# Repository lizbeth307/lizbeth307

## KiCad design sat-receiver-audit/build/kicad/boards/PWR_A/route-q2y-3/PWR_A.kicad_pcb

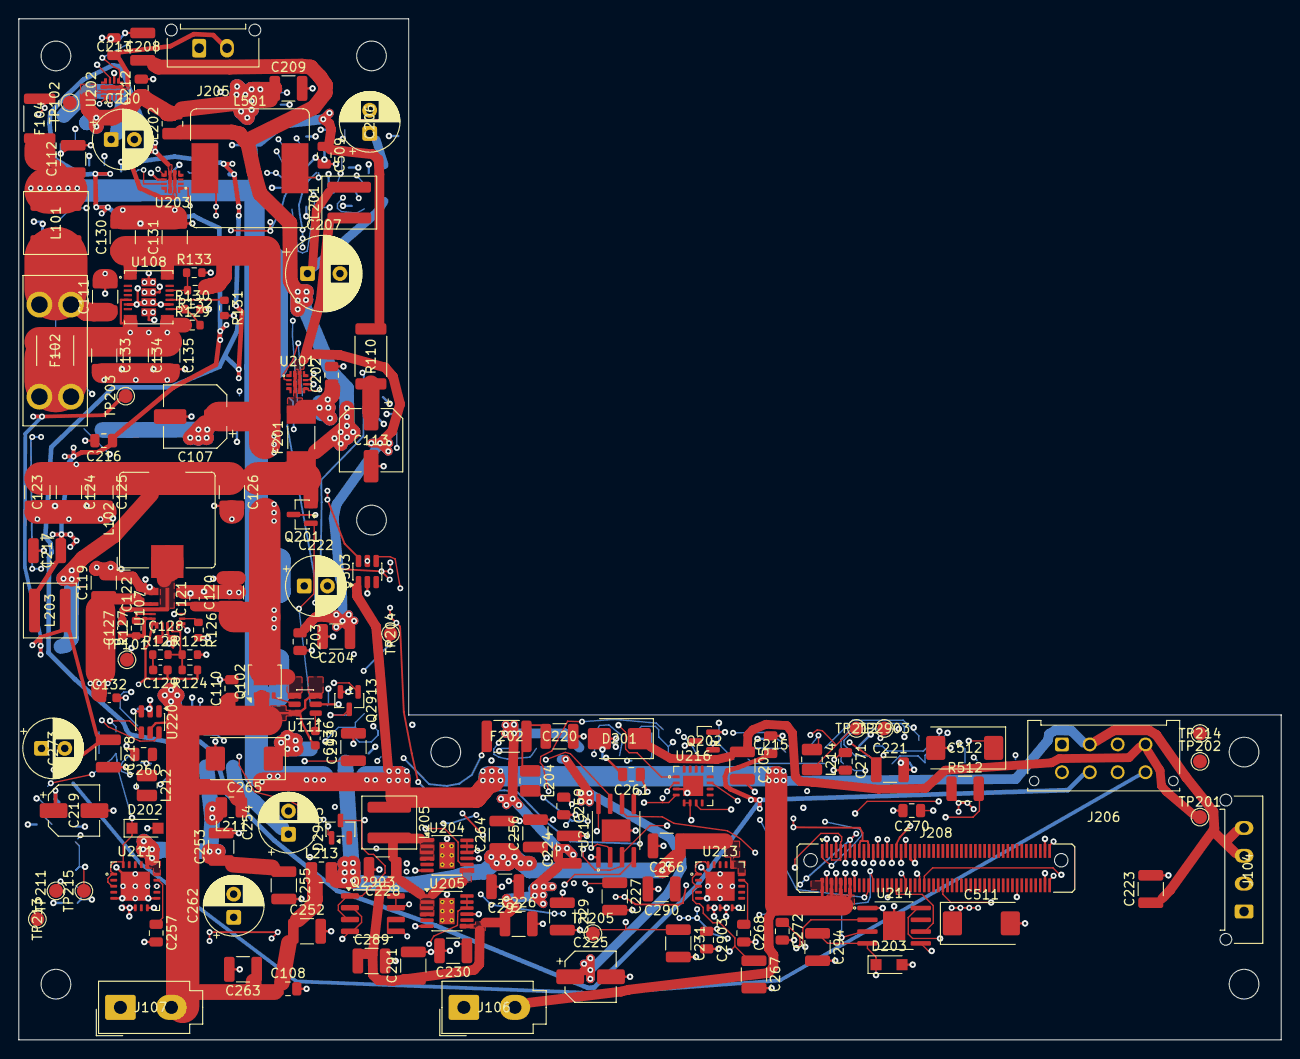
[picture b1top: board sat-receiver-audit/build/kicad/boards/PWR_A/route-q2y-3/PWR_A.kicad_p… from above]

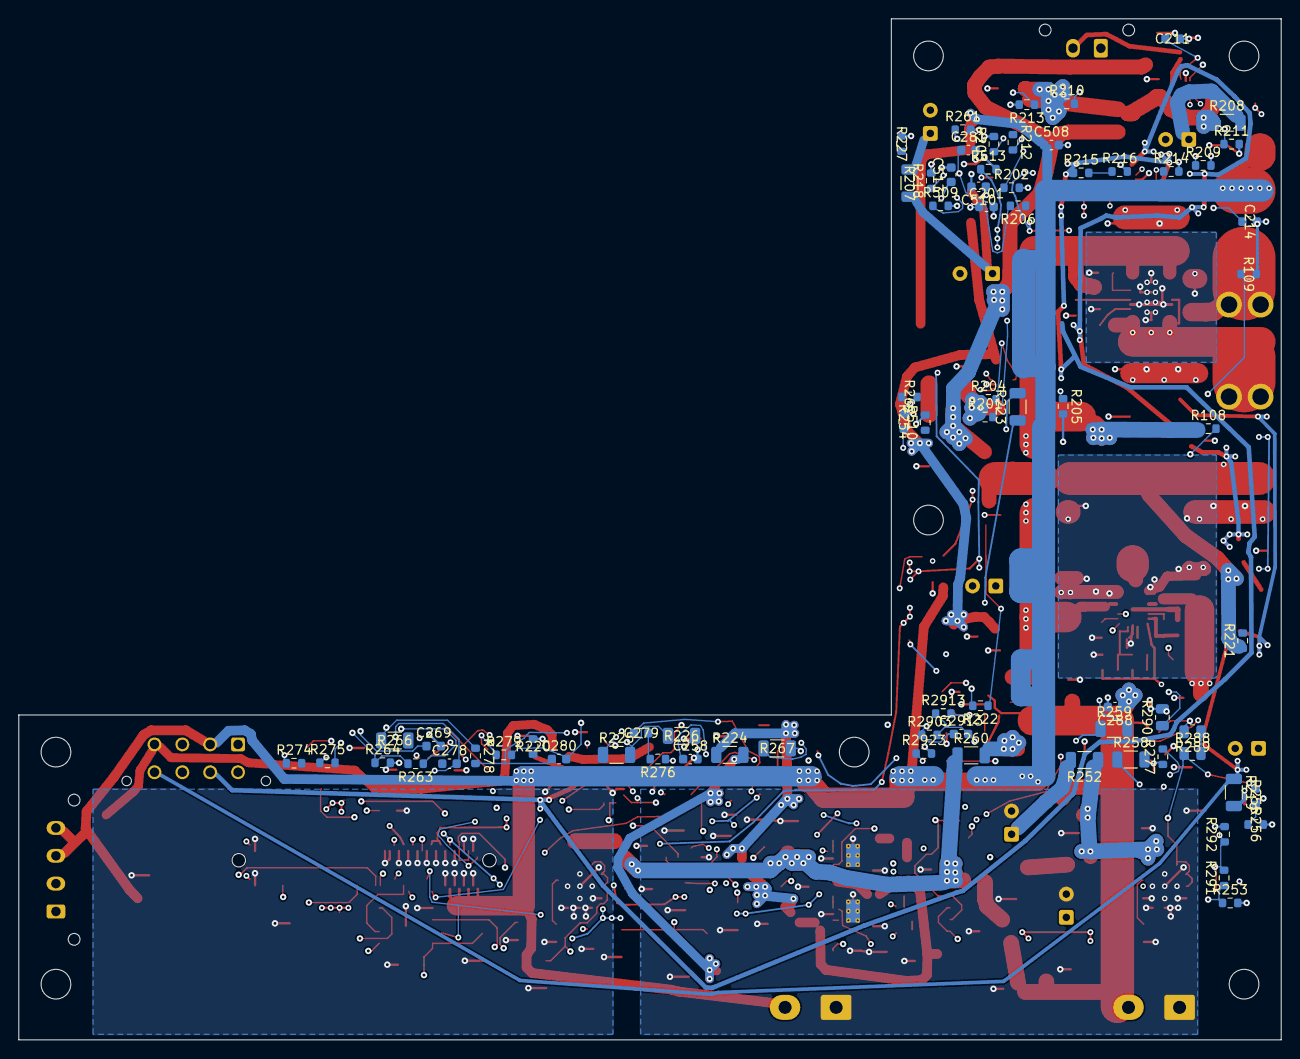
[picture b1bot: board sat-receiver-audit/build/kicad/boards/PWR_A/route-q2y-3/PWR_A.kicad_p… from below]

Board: 6 copper layers, 136.0 x 110.0 mm, 233 parts (73 on the bottom side), 113 nets.

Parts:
C107: 100µF35VlowESR; CP_Elec_6.3x7.7
C108, C110: 1µF50VX7R; C_0805_2012Metric
C111, C112, C123, C124, C125, C126: 22µF50VX7R 1210 C3225X7R1H226M250AC; C_1210_3225Metric
C113: 16SVPC100M 100 µF 16 V ±20% OS-CON; CP_Elec_6.3x5.9
C119, C120, C130, C131: 10µF50VX7R 1210; C_1210_3225Metric
C121, C122, C132: 100nF50VX7R; C_0603_1608Metric
C127: 100nF50VX7R CBOOT; C_0603_1608Metric
C128: 1µF16VX7R CVCC; C_0603_1608Metric
C129: 4.7pF50VC0G CFF; C_0603_1608Metric
C133, C134, C135: 47µF10VX7R 1210; C_1210_3225Metric
C136: 100nF50VX7R VCAP; C_0603_1608Metric
C201, C211, C214: 3.3nF 50V C0G C1608C0G1H332J080AA; C_0603_1608Metric
C202, C203, C212, C213, C215, C216, C257, C259, C260, C261, C268, C270, C271, C272, C2903: 1uF 50V X7R C2012X7R1H105K125AB; C_0805_2012Metric
C204, C205, C208, C209, C217, C218, C220, C221, C226, C228, C230, C252, C253, C255, C263, C264, C266, C289, C291: 10uF 50V X7R C3225X7R1H106K250AC; C_1210_3225Metric
C206, C210, C222, C254, C262, C273: 47uF 50V EEUFR1H470; CP_Radial_D6.3mm_P2.50mm
C207: 220uF/25V UHE1E221MPD; CP_Radial_D8.0mm_P3.50mm
C219, C225: 47uF 10V 16SVPG47M; CP_Elec_5x4.5
C223, C224, C227, C229, C231, C256, C267, C290, C292, C293, C294: 22uF 50V X7R C3225X7R1H226M250AC; C_1210_3225Metric
C258: 47nF 50V X7R C1608X7R1H473K080AA; C_0603_1608Metric
C265: 47uF 35V 35TQS47MEX; CP_EIA-7343-15_Kemet-W
C269, C278, C279, C280, C281, C288, C2913: 100nF 50V X7R C1608X7R1H104K080AA; C_0603_1608Metric
C508, C513: 100nF X7R 10V; C_0603_1608Metric
C509: 4.7uF X7R 10V; C_0805_2012Metric
C510: 1uF X7R 10V; C_0603_1608Metric
C511: 100uF 16V 16TQC100MD2; CP_EIA-7343-20_Kemet-V
C512: 220uF 16V 16TQC220MD3; CP_EIA-7343-31_Kemet-D
D201: SMBJ13A-E3/52; D_SMB_KA
D202, D203: PMEG4030ER; Nexperia_CFP3_SOD-123W
D2903: BZX84C10-7-F; SOT-23
F102: 4 A DC ≥32 V LAB5; Fuseholder_Blade_Mini_Keystone_3568
F104, F202: MF-MSMF075/24-2 0.75A; Fuse_1812_4532Metric
F201: Littelfuse 0451004.MRL 4A; Fuse_Littelfuse-NANO2-451_453
H1, H2, H3, H4, H5, H6, H7: NPTH_3.2mm
J104: X02P1-PWR: Molex Micro-Fit 3.0 4, верхній вхід, S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; Molex_Micro-Fit_3.0_43650-0415_1x04_P3.00mm_Vertical
J106: X42J2-PWR: Molex Mini-Fit Jr. 2×1, верхній вхід, 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; Molex_Mini-Fit_Jr_5566-02A_2x01_P4.20mm_Vertical
J107: X42J1-PWR: Molex Mini-Fit Jr. 2×1, верхній вхід, 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; Molex_Mini-Fit_Jr_5566-02A_2x01_P4.20mm_Vertical
J205: X19P1-PWR: Molex Micro-Fit 3.0 2, верхній вхід, S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; Molex_Micro-Fit_3.0_43650-0215_1x02_P3.00mm_Vertical
J206: SL2-PWR-MF: Molex Micro-Fit 3.0 2×4, верхній вхід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; Molex_Micro-Fit_3.0_43045-0812_2x04_P3.00mm_Vertical
J208: B2B-PWRA: Samtec LSHM-150 2×50, PWR-A верх, стик 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; Samtec_LSHM-150-xx.x-x-DV-N_2x50_P0.50mm_Vertical
L101: XAL6060-103MEC 10 µH ±20%; L_Coilcraft_XAL6060-XXX
L102: SRP1040VA-4R7M 4.7 µH ±20%; L_Bourns_SRP1038C_10.0x10.0mm
L201, L203, L205: 1uH XAL5030-102MEC; L_Coilcraft_XAL5030-XXX
L202, L204, L211, L212, L213, L214: 1uH SRP2510PA-1R0M; L_1008_2520Metric
L501: SRR1260-101M 100uH; L_Bourns_SRR1260
Q102: DMT6007LFG-7; Diodes_PowerDI3333-8
Q201: AO3407A; SOT-23
Q202, Q2913: 2N7002; SOT-23
Q2903: DMP6050SSD-13; SOIC-8_3.9x4.9mm_P1.27mm
R108, R132: 1.00M1%; R_0603_1608Metric
R109: 115k1%; R_0603_1608Metric
R110: WSL2512R3300FEA 0.330 Ω 1%; R_2512_6332Metric
R124: 100k1%; R_0603_1608Metric
R125: 9.09k0.1%; R_0603_1608Metric
R126, R131: 14.3k1%; R_0603_1608Metric
R127: 100Ω1% RBOOT; R_0603_1608Metric
R128: 1.00k1% RFF; R_0603_1608Metric
R129: 40.2k1%; R_0603_1608Metric
R130: 10.0k1%; R_0603_1608Metric
R133: 147k1%; R_0603_1608Metric
R201, R213, R218, R220, R253, R261, R292, R2903: 100k 1%; R_0603_1608Metric
R202: 13.0k 1% 100ppm; R_0603_1608Metric
R203: 825R 1%; R_0603_1608Metric
R204, R210: 102k 0.1%; R_0603_1608Metric
R205, R211, R216: 10.0k 0.1%; R_0603_1608Metric
R206, R212, R221, R222, R2923: 10.0k 1%; R_0603_1608Metric
R207, R208, R223, R252, R259, R260, R267: 0.22R 1% 0.25W; R_1206_3216Metric
R209: 1.96k 1%; R_0603_1608Metric
R214: 1.65k 1%; R_0603_1608Metric
R215: 19.6k 0.1%; R_0603_1608Metric
R219, R224: 0.15R 1% 0.25W; R_1206_3216Metric
R225, R226: 20mR 1% 0.25W; R_1206_3216Metric
R227: 21.5k 0.1% 25ppm; R_0603_1608Metric
R254: 2.05k 1%; R_0603_1608Metric
R255: 110k 0.5%; R_0603_1608Metric
R256: 10.0k 0.5%; R_0603_1608Metric
R258: 0.100R 0.1% 0.25W Kelvin; R_1206_3216Metric
R262: 7.15k 1% 100ppm; R_0603_1608Metric
R263: OVLO TBD (start 102k 0.1%); R_0603_1608Metric
R264: OVLO TBD (start 9.09k 0.1%); R_0603_1608Metric
R266: 0.200R 0.1% 0.25W Kelvin; R_1206_3216Metric
R274, R275, R276, R277, R278, R279: 10.0R 1%; R_0603_1608Metric
R288: TNPW0805332KBYEA 332k 0.1%10ppm; R_0805_2012Metric
R289: TNPW08052K00BYEA 2.00k 0.1%10ppm; R_0805_2012Metric
R290: TNPW080510K0BYEA 10.0k 0.1%10ppm; R_0805_2012Metric
R291: 4.70k 1%; R_0603_1608Metric
R509: RILIM TBD (start 28.7k 1%); R_0603_1608Metric
R510: 100k; R_0603_1608Metric
R512: 1Ohm 0.5W; R_1210_3225Metric
R513: 10k; R_0603_1608Metric
R2913: 22k 1%; R_0603_1608Metric
TP101: PG_SYS12резерв; TestPoint_Pad_D1.5mm
TP102: PG_LAB5резерв; TestPoint_Pad_D1.5mm
TP201: J21; TestPoint_Pad_D1.5mm
TP202: DISP12; TestPoint_Pad_D1.5mm
TP203: LIME3V3; TestPoint_Pad_D1.5mm
TP204: AUX12; TestPoint_Pad_D1.5mm
TP205: LNA4V5; TestPoint_Pad_D1.5mm
TP211: LNB13V2; TestPoint_Pad_D1.5mm
TP212: BONI13V8; TestPoint_Pad_D1.5mm
TP213: E2_FAULT_J21; TestPoint_Pad_D1.5mm
TP214: E2_FAULT_DISP; TestPoint_Pad_D1.5mm
TP215: OVP_LNB_N; TestPoint_Pad_D1.5mm
TP2903: BONI13V8_PORT; TestPoint_Pad_D1.5mm
U107: LM61460AANRJRR; TI_RJR0014A_VQFN-HR-14_4x3.5mm
U108: TPSM63606RDLR — LAB5 default; TI_RDL0020A_B3QFN-20_5x5.5mm
U111: LM74700QDBVRQ1; SOT-23-6
U201, U202, U203: TPS259470ARPWR; TI_RPW0010A_VQFN-HR-10_2x2mm_P0.5mm
U204, U205: LT3045EMSE#PBF; MSOP-12-1EP_3x4.039mm_P0.65mm_EP1.651x2.845mm_ThermalVias
U211, U213: TPS7A4701RGWT; TI_RGW0020A_VQFN-20-1EP_5x5mm_P0.65mm_EP3.15x3.15mm
U212, U214: TPS259630DDAR; TI_DDA0008_HSOP-8-1EP_3.9x4.9mm_P1.27mm_EP2.4x3.1mm
U216: INA3221AIRGVR; TI_RGV0016A_VQFN-16-1EP_4x4mm_P0.65mm_EP2.16x2.16mm
U220: TPS3701DDCR; TSOT-23-6
U503: TPS2553DBVR-1; SOT-23-6

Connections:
3V3_Q6A: C281.1, J208.1, R206.2, R212.2, U216.4, U216.16
AUX12: C221.1, J208.33, L204.2, R223.1, TP204.1
AUX12_DAMP: C222.1, R223.2
BONI13V8: C272.1, J208.25, L214.2, Q2903.7, Q2903.8, R267.1, R2923.1, TP212.1
BONI13V8_DAMP: C273.1, R267.2
BONI13V8_PORT: C2903.1, J208.37, Q2903.5, Q2903.6, TP2903.1
DISP12: C213.1, J205.2, TP202.1, U202.6
E1_CONV_IN: C107.1, C119.1, C120.1, C121.1, C122.1, C130.1, C131.1, C132.1, Q102.5, R108.1, R132.1, U107.8, U107.12, U108.1, U108.16, U111.4
E1_EN_LAB5: R132.2, R133.1, U108.14
E1_EN_SYS12: R108.2, R109.1, U107.7
E1_LAB5_DAMP: C113.1, R110.2
E1_LAB5_FB: R129.2, R130.1, U108.10
E1_LAB5_FUSED: C111.1, F102.2, L101.1
E1_LAB5_RAW: C133.1, C134.1, C135.1, F102.1, R129.1, U108.5, U108.8, U108.9
E1_LAB5_RT: R131.1, U108.12
E1_PG_LAB5: TP102.1, U108.13
E1_PG_SYS12: TP101.1, U107.5
E1_RPP_GATE: Q102.4, U111.5
E1_RPP_VCAP: C136.1, U111.1
E1_SW: C108.1, C110.1, C136.2, C252.1, C263.1, C288.1, J107.2, L211.1, L213.1, Q102.1, Q102.2, Q102.3, U111.3, U111.6, U220.5
E1_SYS12_CBOOT: C127.1, R127.1, U107.14
E1_SYS12_FB: R124.2, R125.1, R128.2, U107.4
E1_SYS12_FF: C129.2, R128.1
E1_SYS12_RBOOT: R127.2, U107.13
E1_SYS12_RT: R126.1, U107.6
E1_SYS12_SW: C127.2, L102.1, U107.10
E1_SYS12_VCC: C128.1, U107.2
E2_AUX_GATE: Q201.1, R221.2, R222.1
E2_AUX_GSINK: Q202.3, R222.2
E2_AUX_PTC: C220.1, F202.2, L204.1
E2_AUX_SWITCHED: F202.1, Q201.3
E2_BLKB_G: C2913.2, D2903.1, Q2903.2, Q2903.4, R2903.2, R2913.1
E2_BLKB_S: C2913.1, D2903.3, Q2903.1, Q2903.3, R2903.1
E2_BLKB_SINK: Q2913.3, R2913.2
E2_BONI_DVDT: C269.1, U214.2
E2_BONI_EF: C270.1, R266.1, R278.1, U214.5
E2_BONI_ILM: R262.1, U214.7
E2_BONI_IN: C264.1, C266.1, L213.2, R260.1, U213.15, U213.16
E2_BONI_IN_DAMP: C265.1, R260.2
E2_BONI_LDO: C267.1, C294.1, D203.1, R263.1, U213.1, U213.3, U213.20, U214.4
E2_BONI_MON: C271.1, L214.1, R266.2, R279.1
E2_BONI_NR: C268.1, U213.14
E2_BONI_OV: R263.2, R264.1, U214.8
E2_DISP_IN: C209.1, C212.1, L202.2, R208.1, R210.1, U202.5
E2_DISP_IN_DAMP: C210.1, R208.2
E2_FAULT_DISP: R212.1, TP214.1, U202.4
E2_FAULT_J21: R206.1, TP213.1, U201.4
E2_J21_EF: C203.1, C204.1, L201.1, U201.6
E2_J21_EN: R201.2, R202.1, U201.1
E2_J21_FUSED: C202.1, F201.2, R201.1, R204.1, U201.5
E2_LIME_EF: C216.1, C217.1, L203.1, U203.6
E2_LNA4_SHUNT: J208.100, R275.1
E2_LNA4_SW: J208.99, R274.1
E2_LNA_IN: C224.1, C226.1, C228.1, C289.1, C291.1, L205.2, R224.1, U204.1, U204.2, U204.3, U204.4, U204.7, U205.1, U205.2, U205.3, U205.4, U205.7
E2_LNA_IN_DAMP: C225.1, R224.2
E2_LNA_SET: C230.1, R227.1, U204.8, U205.8
E2_LNB_DVDT: C258.1, U212.2
E2_LNB_EF: C259.1, R258.1, R276.1, U212.5
E2_LNB_ILM: R254.1, U212.7
E2_LNB_IN: C253.1, C255.1, L211.2, R252.1, U211.15, U211.16
E2_LNB_IN_DAMP: C254.1, R252.2
E2_LNB_LDO: C256.1, C293.1, D202.1, R255.1, R288.1, U211.1, U211.3, U211.20, U212.4
E2_LNB_MON: C260.1, L212.1, R258.2, R277.1
E2_LNB_NR: C257.1, U211.14
E2_LNB_OV: R255.2, R256.1, U212.8
E2_LNB_OV_DIV_MID: R288.2, R289.1
E2_LNB_PRECISE_SENSE: R289.2, R290.1, U220.4
E2_LT_OUT1: C227.1, C290.1, R225.1, U204.10, U204.11, U204.12
E2_LT_OUT2: C229.1, C292.1, R226.1, U205.10, U205.11, U205.12
E2_U201_DVDT: C201.1, U201.7
E2_U201_ILM: R203.1, U201.9
E2_U201_OV: R204.2, R205.1, U201.2
E2_U202_DVDT: C211.1, U202.7
E2_U202_ILM: R209.1, U202.9
E2_U202_OV: R210.2, R211.1, U202.2
E2_U203_DVDT: C214.1, U203.7
E2_U203_ILM: R214.1, U203.9
E2_U203_OV: R215.2, R216.1, U203.2
E2_U216_IM1: C278.2, R275.2, U216.11
E2_U216_IM2: C279.2, R277.2, U216.14
E2_U216_IM3: C280.2, R279.2, U216.1
E2_U216_IP1: C278.1, R274.2, U216.12
E2_U216_IP2: C279.1, R276.2, U216.15
E2_U216_IP3: C280.1, R278.2, U216.2
E5_HFP_DAMP: C512.1, R512.2
E5_U503_ILIM: R509.1, U503.5
E5_VBUS_HFP_SW: C510.1, L501.1, U503.6
EN_AUX12: J208.22, Q202.1, R220.1
EN_BONI: J208.24, Q2913.1, R261.1, U213.13, U214.3
EN_HFP: J208.28, R510.1, U503.3
EN_LIME3V3: J208.26, R218.1, U203.1
EN_LNB: J208.86, R253.1, R291.1, U211.13
FAULT_HFP: J208.32, U503.4
FLT_BONI: J208.34, U214.6
FLT_LIME3V3: J208.36, U203.4
FLT_LNB: J208.38, U212.6
GND: C107.2, C108.2, C110.2, C111.2, C112.2, C113.2, C119.2, C120.2, C121.2, C122.2, C123.2, C124.2, C125.2, C126.2, C128.2, C130.2, C131.2, C132.2, C133.2, C134.2, C135.2, C201.2, C202.2, C203.2, C204.2, C205.2, C206.2, C207.2, C208.2, C209.2, C210.2, C211.2, C212.2, C213.2, C214.2, C215.2, C216.2, C217.2, C218.2, C219.2, C220.2, C221.2, C222.2, C223.2, C224.2, C225.2, C226.2, C227.2, C228.2, C229.2, C230.2, C231.2, C252.2, C253.2, C254.2, C255.2, C256.2, C257.2, C258.2, C259.2, C260.2, C261.2, C262.2, C263.2, C264.2, C265.2, C266.2, C267.2, C268.2, C269.2, C270.2, C271.2, C272.2, C273.2, C281.2, C288.2, C289.2, C290.2, C291.2, C292.2, C293.2, C294.2, C508.2, C509.2, C510.2, C511.2, C512.2, C513.2, C2903.2, D201.A, D202.2, D203.2, J104.1, J104.2, J106.1, J107.1, J205.1, J206.1, J206.3, J206.5, J206.7, J208.3, J208.4, J208.7, J208.8, J208.11, J208.12, J208.15, J208.16, J208.19, J208.23, J208.27, J208.31, J208.35, J208.39, J208.41, J208.97, J208.98, Q202.2, Q2913.2, R109.2, R125.2, R126.2, R130.2, R131.2, R133.2, R202.2, R203.2, R205.2, R209.2, R211.2, R213.2, R214.2, R216.2, R218.2, R220.2, R227.2, R253.2, R254.2, R256.2, R261.2, R262.2, R264.2, R290.2, R292.2, R509.2, R510.2, R513.2, R2923.2, U107.3, U107.9, U107.11, U108.6, U108.11, U108.17, U108.18, U108.19, U108.20, U111.2, U201.8, U202.8, U203.8, U204.6, U204.9, U204.13, U205.6, U205.9, U205.13, U211.5, U211.6, U211.7, U211.8, U211.10, U211.11, U211.EP, U212.1, U212.EP, U213.5, U213.6, U213.7, U213.8, U213.9, U213.10, U213.EP, U214.1, U214.EP, U216.3, U216.EP, U220.2, U220.3, U503.2
I2C2_SCL: J208.44, U216.5, U216.6
I2C2_SDA: J208.46, U216.7
J21: C205.1, C207.1, D201.K, J206.4, L201.2, R207.1, TP201.1
J21_DAMP: C206.1, R207.2
LAB5: C112.1, C223.1, C508.1, C509.1, F104.1, J104.3, J104.4, J106.2, J206.2, J208.2, J208.6, J208.10, J208.14, L101.2, L205.1, R110.1, U503.1
LAB5_RLY: F104.2, J208.17, J208.21
LIME3V3: C218.1, J206.8, L203.2, R219.1, TP203.1
LIME3V3_DAMP: C219.1, R219.2
LNA4V5: C231.1, J208.5, J208.9, R225.2, R226.2, TP205.1
LNB13V2: C261.1, J208.29, L212.2, R259.1, TP211.1
LNB13V2_DAMP: C262.1, R259.2
OVP_LNB_N: J208.54, R291.2, R292.1, TP215.1, U212.3, U220.6
PICO_DISP_EN: J208.56, R213.1, U202.1
SYS12: C123.1, C124.1, C125.1, C126.1, C129.1, C208.1, F201.1, L102.2, L202.1, Q201.2, R124.1, R221.1, U107.1
VBUS_HFP: C511.1, C513.1, J208.13, L501.2, R512.1, R513.1
VCC_3V3_MKEY: C215.1, J206.6, R215.1, U203.5

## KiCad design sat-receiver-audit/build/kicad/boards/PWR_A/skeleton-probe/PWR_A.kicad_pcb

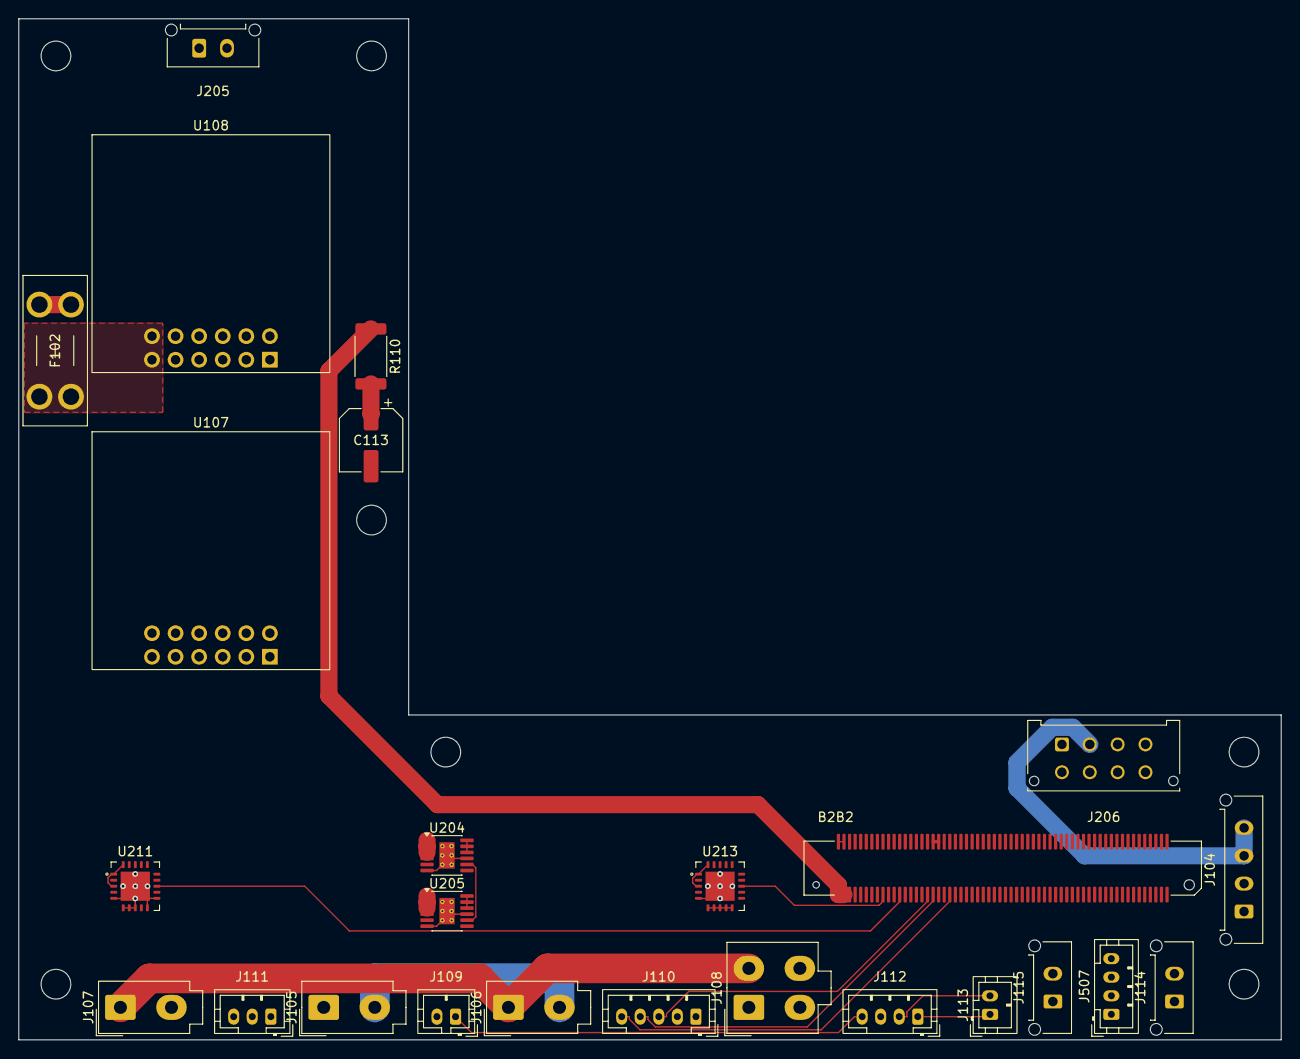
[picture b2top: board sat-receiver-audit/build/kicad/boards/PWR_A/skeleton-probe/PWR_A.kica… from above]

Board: 4 copper layers, 136.0 x 110.0 mm, 32 parts (0 on the bottom side), 27 nets.

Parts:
B2B2: B2B placeholder mate: Samtec QSH-060-01-L-D-A pen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; Hirose_FX8-120S-SV_2x60_P0.6mm
C113: 16SVPC100M 100 µF 16 V ±20% OS-CON; CP_Elec_6.3x5.9
F102: 4 A DC ≥32 V LAB5; Fuseholder_Blade_Mini_Keystone_3568
H1, H2, H3, H4, H5, H6, H7: NPTH_3.2mm
J104: X02P1-PWR: Molex Micro-Fit 3.0 4, верхній вхід, S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; Molex_Micro-Fit_3.0_43650-0415_1x04_P3.00mm_Vertical
J105: X05J1-PWR: Molex Mini-Fit Jr. 2×1, верхній вхід, 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; Molex_Mini-Fit_Jr_5566-02A_2x01_P4.20mm_Vertical
J106: X06J1-PWR: Molex Mini-Fit Jr. 2×1, верхній вхід, 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; Molex_Mini-Fit_Jr_5566-02A_2x01_P4.20mm_Vertical
J107: X07J1-PWR: Molex Mini-Fit Jr. 2×1, верхній вхід, 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; Molex_Mini-Fit_Jr_5566-02A_2x01_P4.20mm_Vertical
J108: X10J1-PWR: Molex Mini-Fit Jr. 2×2, верхній вхід, 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; Molex_Mini-Fit_Jr_5566-04A_2x02_P4.20mm_Vertical
J109: X05S1-PWR: JST PH 2, верхній вхід, S05; JST_PH_B2B-PH-K_1x02_P2.00mm_Vertical
J110: X06S1-PWR: JST PH 5, верхній вхід, S06; JST_PH_B5B-PH-K_1x05_P2.00mm_Vertical
J111: X07S1-PWR: JST PH 3, верхній вхід, S07; JST_PH_B3B-PH-K_1x03_P2.00mm_Vertical
J112: X10S1-PWR: JST PH 4, верхній вхід, S10; JST_PH_B4B-PH-K_1x04_P2.00mm_Vertical
J113: X11S1-PWR: JST PH 2, верхній вхід, S11; JST_PH_B2B-PH-K_1x02_P2.00mm_Vertical
J114: X11P1-PWR: Molex Micro-Fit 3.0 2, верхній вхід, S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; Molex_Micro-Fit_3.0_43650-0215_1x02_P3.00mm_Vertical
J115: X12P1-PWR: Molex Micro-Fit 3.0 2, верхній вхід, S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; Molex_Micro-Fit_3.0_43650-0215_1x02_P3.00mm_Vertical
J205: X19P1-PWR: Molex Micro-Fit 3.0 2, верхній вхід, S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; Molex_Micro-Fit_3.0_43650-0215_1x02_P3.00mm_Vertical
J206: SL2-PWR-MF: Molex Micro-Fit 3.0 2×4, верхній вхід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; Molex_Micro-Fit_3.0_43045-0812_2x04_P3.00mm_Vertical
J507: X32S1-PWR: JST PH 4, верхній вхід, S32; JST_PH_B4B-PH-K_1x04_P2.00mm_Vertical
R110: WSL2512R3300FEA 0.330 Ω 1%; R_2512_6332Metric
U107: Pololu D36V50F12#4095; Pololu_D36V50Fx
U108: Pololu D36V50F5 #4091 — LAB5 default; Pololu_D36V50Fx
U204, U205: LT3045EMSE#PBF; MSOP-12-1EP_3x4.039mm_P0.65mm_EP1.651x2.845mm_ThermalVias
U211, U213: TPS7A4701RGWT; TI_RGW0020A_VQFN-20-1EP_5x5mm_P0.65mm_EP3.15x3.15mm

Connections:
E1_CHG_CC1: J112.1, J113.1
E1_CHG_CC2: J112.2, J113.2
E1_CHG_NTC: J109.1, J112.4
E1_LAB5_DAMP: C113.1, R110.2
E1_LAB5_RAW: F102.1, U108.VOUT
E1_N: J106.1, J107.1, J108.2
E1_SHUNT_P: J105.2, J106.2
E1_SW: J107.2, U107.VIN, U108.VIN
E2_BONI_IN: U213.15, U213.16
E2_BONI_LDO: U213.1, U213.3, U213.20
E2_LNA_IN: U204.1, U204.2, U204.3, U204.4, U204.7, U205.1, U205.2, U205.3, U205.4, U205.7
E2_LNA_SET: U204.8, U205.8
E2_LNB_IN: U211.15, U211.16
E2_LNB_LDO: U211.1, U211.3, U211.20
E2_LT_OUT1: U204.10, U204.11, U204.12
E2_LT_OUT2: U205.10, U205.11, U205.12
EN_BONI: B2B2.103, U213.13
EN_LNB: B2B2.97, U211.13
GND: B2B2.59, B2B2.69, B2B2.82, B2B2.88, B2B2.92, B2B2.96, B2B2.100, B2B2.111, B2B2.116, C113.2, J104.1, J104.2, J105.1, J108.1, J110.1, J111.1, J114.1, J115.1, J205.1, J206.1, J206.3, J206.5, J206.7, J507.1, U107.GND, U108.GND, U204.6, U204.9, U204.13, U205.6, U205.9, U205.13, U211.5, U211.6, U211.7, U211.8, U211.10, U211.11, U211.EP, U213.5, U213.6, U213.7, U213.8, U213.9, U213.10, U213.EP
I2C0_SCL: B2B2.87, J110.3
I2C0_SDA: B2B2.85, J110.4
IMU_RX: B2B2.83, J507.3
IMU_TX: B2B2.81, J507.4
INA228_ALERT: B2B2.79, J110.5
LAB5: B2B2.113, B2B2.115, B2B2.117, B2B2.119, J104.3, J104.4, J206.2, R110.1
LAB5_RLY: B2B2.84, B2B2.86
LNA4V5: B2B2.118, B2B2.120

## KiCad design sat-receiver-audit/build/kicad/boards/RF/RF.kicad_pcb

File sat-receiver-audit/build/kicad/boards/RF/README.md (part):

# RF-плата 184 × 44.5 мм (RF_HMC, RF_HF, RF_INJECTOR, DC_CORE) — W2 PCB-RF-1, PCB-RF-2

**Статус: `RF2_ROUTED_NOT_FOR_FABRICATION`.** Усі 172 посилання RF-доменів розміщені; RF50, GND, вузли SENSE і CHASSIS задані скриптом і заблоковані; решту розводить Freerouting лише на F.Cu і B.Cu. Закомічений прогін sr-rx-pcb 43129454692 (повторне розведення 43105422139 на смузі wip/w2-int після злиття B2B, той самий результат): DRC — 0 помилок, 0 не з'єднаних, `ignored_checks` []; у кожній HMC7992 — 5 переходів під EPAD (STACK.md:299); `pcb/check_boards.py` — 0 знахідок, разом із незалежними перевірками вузлів RF на розведеній платі (`rf_nodes`: відводи, перші 100 pF, зона DC_CORE, довжина SENSE, стяжка на BOND-RF); набір файлів виробництва — `fab/`, разом із купоном імпедансу. Це результат CI/моделі, а не випуск у виробництво: жодні апаратні чи стендові ворота (RF-01…03, DC-01…05, E4-04, E4-07) цим не закриваються.

## Файли

| Файл | Що це |
|---|---|
| `rf_layout.py` | джерело розміщення: якорі, ряди, траси RF50, мідь SENSE, перевірки геометрії; пише `../../../../pcb/boards/RF.json` і `RF.kicad_pro` |
| `rf_copper.py` | скриптова мідь PCB-RF-2: входи RF50 у площадки, переходи GND (EPAD, виходи площадок, огорожі RF50, кільця HMC, зшивання), вихід BIAS_CH4, купон |
| `../../../../pcb/boards/RF.json` | специфікація плати для `pcb/board_gen.py` і `pcb/check_boards.py` (згенерована `rf_layout.py`, вручну не правити) |
| `RF.kicad_pro` | проєкт KiCad: класи цілей і перевірені рівні DRC (згенерований `rf_layout.py`) |
| `RF.kicad_pcb`, `report.json`, `drc.json`, `connectors.json`, `route-log.json`, `RF-top.svg`, `RF-bottom.svg` | виходи прогону `[pcb-route RF]` у sr-rx-pcb (§2: тільки патчем `pcb-regenerated-RF`, комітом `GENERATED:`) |
| `review.json` | незалежна перевірка `pcb/check_boards.py --board RF` (стандартна бібліотека), разом із перевіркою `rf_nodes` за ключем специфікації `rf_checks` |
| `fab/` | набір виробництва `pcb/fab_export.py`: Gerber X2, свердління PTH/NPTH і карти, IPC-D-356, CPL і BOM для JLC, примітки з рядком контролю імпедансу; плата й обидва купони в одному наборі — примітки, README набору й `manifest.json` (`coverage.coupons`) називають три частини Edge.Cuts, а розмір і площу плати беруть лише з її контуру |

Перегенерувати специфікацію (з `sat-receiver-audit`): `python3 build/kicad/boards/RF/rf_layout.py` і `--check`. Потрібна тека бібліотеки KiCad 10.0.7 у `KICAD10_FOOTPRINT_DIR` (два футпринти-заглушки U.FL, SHA256 звіряється). Скрипт перед записом перевіряє: перекриття кортиярдів, площадки проти краю 0.3 мм і зон отворів ⌀7.0, зазори скриптової міді до чужих площадок і трас за класами (RF50 0.20, DCTAP і DCSENSE 0.30, інші 0.15), відстань площадка–площадка, розв'язку ≤ 2 мм, що кожна площадка цілі RF50 сидить на скриптовій міді, крок огорожі RF50 ≤ 2.0 мм (правило `pcb/check_boards.py`), довжину міді SENSE проти прототипу, відводи ≤ 2 мм і відведення поза зоною DC_CORE. Ті самі межі скрипт пише в ключ `rf_checks` специфікації, і `pcb/check_boards.py` міряє їх ще раз на розведеному `RF.kicad_pcb` (див. «Незалежні перевірки RF»).

## Розміщення (координати плати, мм, y угору, вид з боку компонентів)

- **Верхній край (y 44.5):** U.FL J425 (P6) x 38.4, J424 (P3) x 98.0, J423 (P2) x 107.0, J427 (P8) x 114.0; крайові SMA J426 (ch5 ПЧ) x 26.0, J409 (BENCH) x 52.6, J411 (RTL-B) x 65.25, J412 (RX1 Lime) x 78.25, J410 (RTL-A) x 123.0. Межа плати для SMA — x = −4.76 мм футпринта.
- **HMC7992:** U406 (RTL-B) (65.5, 27) кут 0, U407 (Lime) (79, 27) кут 270, U405 (RTL-A) (123.25, 27) кут 0; усі 15 розділових конденсаторів RF-виводів (RF-01) стоять у лінії RF50, навантаження 49.9 Ом (PARK) — поруч із виводами; керування 1 k / 100 k / 100 pF і 100 nF VDD — під або біля кожного перемикача.
- **Порти й інжектори (DC-01):** відвід 26.7 k (R4420/R4430/R4440) з першим 100 pF, інжекторна котушка і перший відвідний резистор 249 Ом стоять площадкою 1 на самій лінії RF50 біля порту (P2 x 107, P3 x 98, HF_CM — заглушка PH405 на нижньому краї); решта ланцюжків 4 × 249 Ом — поряд. Відстань від відведень до зони DC_CORE (кортиярди DC_CORE + 5 мм; 5 мм — вибір проєкту, DC-01/DC-02 відстані не задають) — 21.49 мм від центру кортиярду відведення (`rf_layout.py`, `rf_copper.bleed_to_dc_core_keepout_mm` специфікації) і 19.91 мм від краю кортиярду (`review.json`, `rf_nodes`). Так само перший 100 pF: 0.67 мм від кортиярду C44x0 до центру площадки 2 відводу (`rf_layout.py`) і 0.55 мм між краями площадок (`review.json`). C446 (розв'язка BIAS_CH4) — ліворуч від виводу 1 A424, поза огорожею E4_P2.
- **HF-реле:** K401 (16, 20) кут 0, K402 (40, 20) кут 180; HF_LINK і VHF_LINK — перемички між контактами 4 і 5 кожного реле; RELAY_STAGE обходить праворуч; драйвери Q401/Q402/D401/R412–R415 — над реле.
- **DC_CORE (x 132–152, блоки каналів UHF y 34.3, LBAND 23.7, HF 13.1):** у кожному блоці два TLV3012 (U451-тип, кут 90, і U450-тип, кут 270) стоять входами IN− і IN+ один до одного на відстані 1.6 мм; над ними — дільник 23.2 k / 49.9 k, фільтр 10 nF і обмежувач BAV199; праворуч — пари 100 Ом / 100 k і AO3400A; 100 nF — біля виводу V+ кожного компаратора (DC-03). Опорний блок (D450, LM4040 U458, дільники) і блоки «опора в нормі» U456/U457 — праворуч (x 157–176). Позиції прототипу (59 × 67 мм) на 44.5 мм не вміщаються; збережено склад і групування каналів.
- **Джгути S03/S04:** J419 (S4B) x 122, J418 (S8B) x 134.95, J420 (S8B) x 155, отворами до нижнього краю; траси S03/S04 доходять до нижнього краю RF-плати при x 163.3 і 167.5 (`mechanical/generated/harness-routes.json`).
- **GND/CHASSIS (BOND-RF):** контрактний отвір H5 (92, 40.5) металізований — отвір 3.2 мм, площадка 7.0 мм (діаметр зони утримання) на всіх шарах, маска відкрита, коло CHASSIS (`bond_hole` у специфікації). NT401 (92, 33.4) стоїть площадкою CHASSIS на межі зони утримання й з'єднаний з площадкою H5 доріжкою 1.0 мм — єдина стяжка GND–CHASSIS. Інші п'ять отворів — NPTH без кола. Заглушки PH407 більше немає.

## Мідь

- **RF50 (скриптова, заблокована, F.Cu):** 90 (68 доріжок, з них 15 входів 0.25 мм у виводи HMC) відрізків CPWG 0.36 мм, зазор до заливки GND 0.20 мм; кожна ціль RF50 з'єднана від площадки до площадки; біля виводів HMC — вхід 0.25 мм на 0.84 мм (`rf50_taper`). Кінці ліній заходять у площадки на 0.2 мм від їхнього краю, площадки на лінії ділять лінію на шматки (площадка — сама лінія, CPWG там немає; так ділянки, що перевіряються, починаються поза площадками).
- **Скриптові переходи (0.6/0.3 мм, заблоковані), усього 1092 — 1091 GND і вихід BIAS_CH4:** 16 під відкритими площадками (у кожній HMC7992 — 5: центр і чотири кути на ±0.54 мм, бо STACK.md:299 вимагає ≥5 переходів в EPAD; крок центр–кут 0.764 мм ≥ 0.75 = `min_hole_to_hole` 0.45 + свердло 0.3; один в A407; розташування — вибір проєкту, бо паспорт ADI не прочитався, див. нижче; `rf_layout.py` перевіряє ≥5 на кожну HMC7992), 116 виходів площадок GND із короткими відрізками (місце з найменшою кількістю чужої міді поруч), 567 огорожі RF50 (обидва боки кожного відрізка, крок ≈ 1.0 мм, 0.72–1.3 мм від осі; найбільший розрив за правилом `check_boards` — ≤ 2.0 мм на всіх відрізках), 44 кільця навколо кожної секції HMC7992 (резерв під екран), 348 зшивання (сітка 3.5 мм поза кортиярдами). Виводи GND QFN, яким не заважають сусіди, з'єднані з відкритою площадкою короткими відрізками (15); кутові виводи GND — заливкою.
- **SENSE (DC_CORE):** скриптова мідь 0.20 мм, 7.475 мм на коло проти 17.641 мм у прототипі (`verification/pcb-prototype-review.json`, сума відрізків кола); клас проєкту DCSENSE 0.20/0.30 — заливка GND тримає 0.30 мм навколо (охорона) над суцільною In1.Cu.
- **BIAS_CH4:** C446.1 → A424.1 доріжкою 0.35 мм і скриптовий перехід виходу на B.Cu (прогін 42421969829 лишив коло нерозведеним усередині огорож E4_P2 і E4_CH4_RF_ONLY); далі розводить Freerouting.
- **Шари:** In1.Cu і In2.Cu — шари типу power із суцільною GND (заливки до розведення, з'єднання площадок суцільне), тож маршрутизатор ставить крізь них лише переходи; заливки GND на F.Cu (копланарна земля) і B.Cu — після розведення (SMD-площадки суцільно, THT — зі спицями).
- **Маршрутизатор:** Freerouting 2.5.0 розводить решту (керування, живлення інжекторів, DCTAP, DC_CORE) на F.Cu і B.Cu; класи RF50, DCSENSE і SCRIPTED (GND, CHASSIS) він пропускає (`-inc`), свій fan-out вимкнено (його відгалуження звужувалися до 0.12 мм). Кінці доріжок маршрутизатора, що закінчуються всередині переходу не в центрі, `pcb/board_gen.py` з'єднує з центром коротким відрізком (`via_centre_stubs` у `route-log.json`).
- **Заливки** беруть типові параметри зон із `RF.kicad_pro`: зазор 0.20 мм (= зазор CPWG RF50), мінімальна ширина 0.25, тепловий зазор 0.25, спиці 0.30. `min_hole_to_hole` 0.45 — поріг JLC для отворів площадок.

## Купон імпедансу (окремі контури в тому самому наборі)

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
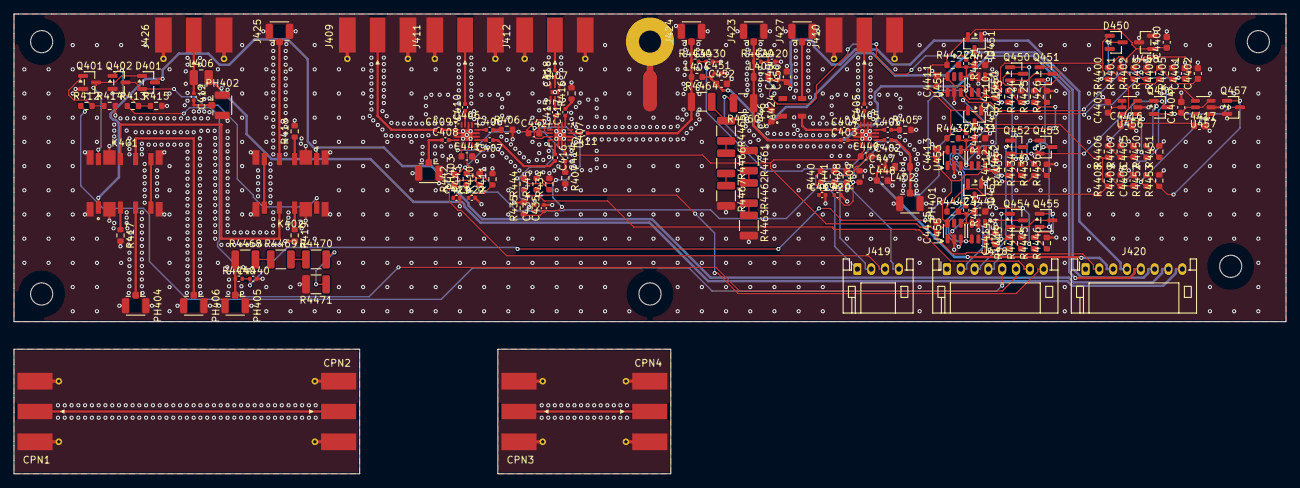
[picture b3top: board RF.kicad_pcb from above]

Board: 4 copper layers, 184.0 x 44.5 mm, 188 parts (0 on the bottom side), 122 nets.

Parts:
A407: YAT-10A+ 10 dB; MiniCircuits_MC1630_MCLP-6-1EP_2x2mm_P0.65mm
A424: TCBT-2R5G+ ch4; MiniCircuits_GU1604_3.81x3.81mm
C401, C402, C403, C404, C405: 1 nF C0G 50 V 0402; C_0402_1005Metric
C406, C407, C408, C409, C410, C411, C412, C414, C415, C416, C417, C419, C420, C421, C422, C434, C435: 100 pF C0G 50 V 0402; C_0402_1005Metric
C418: 22 pF C0G 50 V 0402; C_0402_1005Metric
C440, C441, C442, C4400: 100 nF X7R 10 V; C_0603_1608Metric
C446: 10 nF X7R 50 V external DC bypass; C_0603_1608Metric
C447, C449, C451, C4420, C4430, C4440: 100 pF C0G 50 V; C_0402_1005Metric
C448, C450, C452, C4401, C4402, C4405, C4406, C4421, C4431, C4441: 10 nF C0G 50 V; C_0603_1608Metric
C4403, C4404: 1 nF C0G 50 V; C_0603_1608Metric
C4410, C4411, C4412, C4413, C4414, C4415, C4416, C4417: 100 nF X7R 10 V local decoupling; C_0603_1608Metric
CPN1, CPN2, CPN3, CPN4: Molex 73251-1153 (coupon, hand-fitted for the ben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; SMA_Molex_73251-1153_EdgeMount_Horizontal_CS
D401: BAT54C; SOT-23
D450: BAV199 reference reverse-feed isolation; SOT-23
D451, D452, D453: BAV199 sense clamps; SOT-23
H1, H2, H3, H4, H6: NPTH_3.2mm
H5: PTH_BOND_3.2mm_7mm
J409: BENCH internal SMA; SMA_Molex_73251-1153_EdgeMount_Horizontal_CS
J410: RTL-A RF internal SMA; SMA_Molex_73251-1153_EdgeMount_Horizontal_CS
J411: RTL-B RF internal SMA; SMA_Molex_73251-1153_EdgeMount_Horizontal_CS
J412: RX1 edge SMA; SMA_Molex_73251-1153_EdgeMount_Horizontal_CS
J418: X03S1-RF: JST PH 8, боковий вхід, S03; JST_PH_S8B-PH-K_1x08_P2.00mm_Horizontal
J419: X03S2-RF: JST PH 4, боковий вхід, S03; JST_PH_S4B-PH-K_1x04_P2.00mm_Horizontal
J420: X04S1-RF: JST PH 8, боковий вхід, S04; JST_PH_S8B-PH-K_1x08_P2.00mm_Horizontal
J423: P2 board U.FL: 4.3 V; U.FL_Hirose_U.FL-R-SMT-1_Vertical_CS
J424: P3 board U.FL: 4.3 V; U.FL_Hirose_U.FL-R-SMT-1_Vertical_CS
J425: P6 board U.FL: no DC; U.FL_Hirose_U.FL-R-SMT-1_Vertical_CS
J426: ch5 IF edge SMA: 13.2 V LNB; SMA_Molex_73251-1153_EdgeMount_Horizontal_CS
J427: P8 board U.FL: ch4 4.3 V; U.FL_Hirose_U.FL-R-SMT-1_Vertical_CS
K401: G6K-2F-RF-S DC5 HF; Relay_DPDT_Omron_G6K-2F-RF-S
K402: G6K-2F-RF-S DC5 VHF; Relay_DPDT_Omron_G6K-2F-RF-S
L402: Coilcraft 0805LS-471XGRC 470 nH 2%; L_0805_2012Metric
L403: Coilcraft 0805HP-221XGRC 220 nH 2%; L_0805_2012Metric
L404: Coilcraft 0603HP-47NXGRW 47 nH 2%; L_0603_1608Metric
L406: LQW2UAS68NG00L 68 nH 1 A; L_1008_2520Metric
NT401: RF ground / CHASSIS bond; NetTie-2_SMD_Pad2.0mm
PH401: A402 SAWbird+ NOAA OUT (E4_RF_CH1) board end, pla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; U.FL_Hirose_U.FL-R-SMT-1_Vertical
PH402: A405 VAT attenuator IN (E4_RF_CH5_DC) board end, 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; U.FL_Hirose_U.FL-R-SMT-1_Vertical
PH403: A405 VAT attenuator OUT (E4_RF_CH5_ATT) board end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; U.FL_Hirose_U.FL-R-SMT-1_Vertical
PH404: A406 Boni bias-tee RF port (E4_HF_BT) board end, 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; U.FL_Hirose_U.FL-R-SMT-1_Vertical
PH405: W408 OUT / A406 ANT tap point (E4_HF_CM) board en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; U.FL_Hirose_U.FL-R-SMT-1_Vertical
PH406: A414 Airspy HF+ ANT (E4_HFP_ANT) board end, place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; U.FL_Hirose_U.FL-R-SMT-1_Vertical
Q401, Q402, Q450, Q451, Q452, Q453, Q454, Q455, Q456, Q457: AO3400A; SOT-23
R405, R406, R407, R416, R417, R418, R419: 49.9Ω 1% RF load; R_0603_1608Metric
R408, R409, R410, R411, R414, R415, R434, R435: 100kΩ 1%; R_0603_1608Metric
R412, R413: 100Ω; R_0603_1608Metric
R440, R441, R442, R443, R444, R445: 1kΩ 1%; R_0603_1608Metric
R4400: 150 Ω 1% 0.125 W; R_0603_1608Metric
R4401: 10 kΩ 1% Q6A off-state bleed; R_0603_1608Metric
R4402, R4405: 26.7 kΩ 0.1%; R_0603_1608Metric
R4403, R4404: 25.5 kΩ 0.1%; R_0603_1608Metric
R4406: 10.0 kΩ 0.1%; R_0603_1608Metric
R4407, R4408: 24.9 kΩ 0.1%; R_0603_1608Metric
R4409: 33.2 kΩ 0.1%; R_0603_1608Metric
R4420, R4430, R4440: 26.7 kΩ 0.1% 0402 RF tap; R_0402_1005Metric
R4421, R4431, R4441: 23.2 kΩ 0.1% 0402; R_0402_1005Metric
R4422, R4432, R4442: 49.9 kΩ 0.1%; R_0603_1608Metric
R4423, R4425, R4433, R4435, R4443, R4445, R4450, R4452: 100 Ω; R_0603_1608Metric
R4424, R4426, R4434, R4436, R4444, R4446, R4451, R4453: 100 kΩ; R_0603_1608Metric
R4460, R4461, R4462, R4463, R4464, R4465, R4466, R4467, R4468, R4469, R4470, R4471: 249 Ω 1% ≥0.5 W; R_1210_3225Metric
U405: HMC7992LP3DE A; QFN-16-1EP_3x3mm_P0.5mm_EP1.7x1.7mm_EPAD
U406: HMC7992LP3DE B; QFN-16-1EP_3x3mm_P0.5mm_EP1.7x1.7mm_EPAD
U407: HMC7992LP3DE C; QFN-16-1EP_3x3mm_P0.5mm_EP1.7x1.7mm_EPAD
U450, U451, U452, U453, U454, U455, U456, U457: TLV3012BIDBVR; SOT-23-6
U458: LM4040A20IDBZR 2.048 V 0.1% shunt; SOT-23

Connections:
3V3_Q6A: C440.1, C441.1, C442.1, C4410.1, C4411.1, C4412.1, C4413.1, C4414.1, C4415.1, C4416.1, C4417.1, D450.1, J420.2, R4401.1, U405.6, U406.6, U407.6, U450.6, U451.6, U452.6, U453.6, U454.6, U455.6, U456.6, U457.6
BIAS_CH1: C447.1, C448.1, J420.3, L402.2
BIAS_CH2_PORT: C449.1, C450.1, J420.4, L403.2
BIAS_CH3_PORT: C451.1, C452.1, J420.5, L404.2
BIAS_CH4: A424.1, C446.1, J420.6
CHASSIS: H5.1, NT401.2
CPN_GND_25: CPN3.SHIELD, CPN4.SHIELD
CPN_GND_50: CPN1.SHIELD, CPN2.SHIELD
CPN_THRU_25: CPN3.CENTER, CPN4.CENTER
CPN_THRU_50: CPN1.CENTER, CPN2.CENTER
DCS_HF: J418.2, Q454.3
DCS_LBAND: J418.3, Q452.3
DCS_UHF: J418.4, Q450.3
E4_BENCH: C409.1, J409.CENTER
E4_CH4_RF_ONLY: A424.4, C404.1
E4_DCS_HF_BLEED_1: R4468.2, R4469.1
E4_DCS_HF_BLEED_2: R4469.2, R4470.1
E4_DCS_HF_BLEED_3: R4470.2, R4471.1
E4_DCS_HF_HIGH_GATE: Q455.1, R4445.2, R4446.1
E4_DCS_HF_HIGH_OK: R4445.1, U455.1
E4_DCS_HF_LOW_GATE: Q454.1, R4443.2, R4444.1
E4_DCS_HF_LOW_OK: R4443.1, U454.1
E4_DCS_HF_SENSE: C4441.1, D453.3, R4441.2, R4442.2, U454.3, U455.4
E4_DCS_HF_SINK_MID: Q454.2, Q455.3
E4_DCS_HF_TAP: C4440.1, R4440.2, R4441.1
E4_DCS_HIGH: C4402.1, R4404.2, R4405.1, U451.3, U453.3, U455.3
E4_DCS_LBAND_BLEED_1: R4464.2, R4465.1
E4_DCS_LBAND_BLEED_2: R4465.2, R4466.1
E4_DCS_LBAND_BLEED_3: R4466.2, R4467.1
E4_DCS_LBAND_HIGH_GATE: Q453.1, R4435.2, R4436.1
E4_DCS_LBAND_HIGH_OK: R4435.1, U453.1
E4_DCS_LBAND_LOW_GATE: Q452.1, R4433.2, R4434.1
E4_DCS_LBAND_LOW_OK: R4433.1, U452.1
E4_DCS_LBAND_SENSE: C4431.1, D452.3, R4431.2, R4432.2, U452.3, U453.4
E4_DCS_LBAND_SINK_MID: Q452.2, Q453.3
E4_DCS_LBAND_TAP: C4430.1, R4430.2, R4431.1
E4_DCS_LOW: C4401.1, R4402.2, R4403.1, U450.4, U452.4, U454.4
E4_DCS_REF: C4400.1, D451.2, D452.2, D453.2, R4400.2, R4402.1, R4404.1, R4406.1, R4408.1, R4422.1, R4432.1, R4442.1, U458.1
E4_DCS_REF12_HIGH: C4404.1, U457.3, U457.5
E4_DCS_REF12_LOW: C4403.1, U456.4, U456.5
E4_DCS_REF_FEED: D450.3, R4400.1
E4_DCS_REF_GATE_HIGH: Q457.1, R4452.2, R4453.1
E4_DCS_REF_GATE_LOW: Q456.1, R4450.2, R4451.1
E4_DCS_REF_GOOD_HIGH: R4452.1, U457.1
E4_DCS_REF_GOOD_LOW: R4450.1, U456.1
E4_DCS_REF_PG_HIGH: C4406.1, R4408.2, R4409.1, U457.4
E4_DCS_REF_PG_LOW: C4405.1, R4406.2, R4407.1, U456.3
E4_DCS_REF_RETURN_MID: Q456.2, Q457.3
E4_DCS_RETURN: Q451.2, Q453.2, Q455.2, Q456.3
E4_DCS_UHF_BLEED_1: R4460.2, R4461.1
E4_DCS_UHF_BLEED_2: R4461.2, R4462.1
E4_DCS_UHF_BLEED_3: R4462.2, R4463.1
E4_DCS_UHF_HIGH_GATE: Q451.1, R4425.2, R4426.1
E4_DCS_UHF_HIGH_OK: R4425.1, U451.1
E4_DCS_UHF_LOW_GATE: Q450.1, R4423.2, R4424.1
E4_DCS_UHF_LOW_OK: R4423.1, U450.1
E4_DCS_UHF_SENSE: C4421.1, D451.3, R4421.2, R4422.2, U450.3, U451.4
E4_DCS_UHF_SINK_MID: Q450.2, Q451.3
E4_DCS_UHF_TAP: C4420.1, R4420.2, R4421.1
E4_HFP_ANT: K401.6, PH406.1
E4_HF_BT: K401.3, PH404.1
E4_HF_CM: PH405.1, R4440.1, R4468.1
E4_HF_LINK: K401.4, K401.5
E4_K1_G: Q401.1, R412.2, R414.1
E4_K1_LS: D401.1, K401.8, Q401.3
E4_K2_G: Q402.1, R413.2, R415.1
E4_K2_LS: D401.2, K402.8, Q402.3
E4_LIME_CTL_A: C434.1, R434.1, R444.2, U407.8
E4_LIME_CTL_B: C435.1, R435.1, R445.2, U407.7
E4_LIME_RF1: C414.1, U407.12
E4_LIME_RF3: C415.1, U407.4
E4_LIME_RFC: C411.2, U407.15
E4_LIME_RFSPARE: C417.1, U407.1
E4_LIME_TO_RTLB: C416.1, U407.9
E4_P2: C403.1, J423.CENTER, L403.1, R4420.1, R4460.1
E4_P3: C411.1, J424.CENTER, L404.1, R4430.1, R4464.1
E4_P6: J425.CENTER, K402.3
E4_PARK_A: C401.2, R405.1
E4_PARK_B: C406.2, R406.1
E4_PARK_C: C414.2, R407.1
E4_PARK_C_SPARE: C417.2, R416.1
E4_PARK_HF: K401.2, R417.1
E4_PARK_HFP: K402.7, R419.1
E4_PARK_VHF: K402.2, R418.1
E4_RELAY_STAGE: K401.7, K402.6
E4_RFC_A: C405.2, J410.CENTER
E4_RFC_B: C410.2, J411.CENTER
E4_RF_CH1: C402.1, L402.1, PH401.1
E4_RF_CH3_B: C407.1, C416.2
E4_RF_CH4: A424.3, J427.CENTER
E4_RF_CH5: C412.1, J426.CENTER, L406.1
E4_RF_CH5_ATT: C408.1, PH403.1
E4_RF_CH5_DC: C412.2, PH402.1
E4_RTLA_CTL_A: C419.1, R408.1, R440.2, U405.8
E4_RTLA_CTL_B: C420.1, R409.1, R441.2, U405.7
E4_RTLA_RF1: C401.1, U405.12
E4_RTLA_RF2: C402.2, U405.9
E4_RTLA_RF3: C403.2, U405.4
E4_RTLA_RF4: C404.2, U405.1
E4_RTLA_RFC: C405.1, U405.15
E4_RTLB_CTL_A: C421.1, R410.1, R442.2, U406.8
E4_RTLB_CTL_B: C422.1, R411.1, R443.2, U406.7
E4_RTLB_RF1: C406.1, U406.12
E4_RTLB_RF2: C407.2, U406.9
E4_RTLB_RF3: C408.2, U406.4
E4_RTLB_RF4: C409.2, U406.1
E4_RTLB_RFC: C410.1, U406.15
E4_RX1_EDGE: C418.2, J412.CENTER
E4_VHF_LINK: K402.4, K402.5
E4_YAT_IN: A407.2, C415.2
E4_YAT_OUT: A407.5, C418.1
GND: A407.1, A407.3, A407.4, A407.6, A407.EP, C419.2, C420.2, C421.2, C422.2, C434.2, C435.2, C440.2, C441.2, C442.2, C446.2, C447.2, C448.2, C449.2, C450.2, C451.2, C452.2, C4400.2, C4401.2, C4402.2, C4403.2, C4404.2, C4405.2, C4406.2, C4410.2, C4411.2, C4412.2, C4413.2, C4414.2, C4415.2, C4416.2, C4417.2, C4420.2, C4421.2, C4430.2, C4431.2, C4440.2, C4441.2, D451.1, D452.1, D453.1, J409.SHIELD, J410.SHIELD, J411.SHIELD, J412.SHIELD, J418.1, J420.1, J423.SHIELD, J424.SHIELD, J425.SHIELD, J426.SHIELD, J427.SHIELD, K401.G1, K401.G2, K402.G1, K402.G2, NT401.1, PH401.2, PH402.2, PH403.2, PH404.2, PH405.2, PH406.2, Q401.2, Q402.2, Q457.2, R405.2, R406.2, R407.2, R408.2, R409.2, R410.2, R411.2, R414.2, R415.2, R416.2, R417.2, R418.2, R419.2, R434.2, R435.2, R4401.2, R4403.2, R4405.2, R4407.2, R4409.2, R4424.2, R4426.2, R4434.2, R4436.2, R4444.2, R4446.2, R4451.2, R4453.2, R4463.2, R4467.2, R4471.2, U405.2, U405.3, U405.5, U405.10, U405.11, U405.13, U405.14, U405.16, U405.EPAD, U406.2, U406.3, U406.5, U406.10, U406.11, U406.13, U406.14, U406.16, U406.EPAD, U407.2, U407.3, U407.5, U407.10, U407.11, U407.13, U407.14, U407.16, U407.EPAD, U450.2, U451.2, U452.2, U453.2, U454.2, U455.2, U456.2, U457.2, U458.2, U458.3
K1_ON: J418.5, R412.1
K2_ON: J418.6, R413.1
LAB5_RLY: D401.3, J420.7, K401.1, K402.1
LNB13V2: J420.8, L406.2
SW_LIME_A: J418.7, R444.1
SW_LIME_B: J418.8, R445.1
SW_RTLA_A: J419.1, R440.1
SW_RTLA_B: J419.2, R441.1
SW_RTLB_A: J419.3, R442.1
SW_RTLB_B: J419.4, R443.1
